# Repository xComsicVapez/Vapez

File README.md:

# Vapez

## Wooting 60HE — Apex Superglide DKS

Profile + setup for one-key superglides on **`C`** at **240 FPS** (Jump=`Space`, Crouch=`Left Ctrl`):

→ [`wooting-apex-superglide/`](./wooting-apex-superglide/)

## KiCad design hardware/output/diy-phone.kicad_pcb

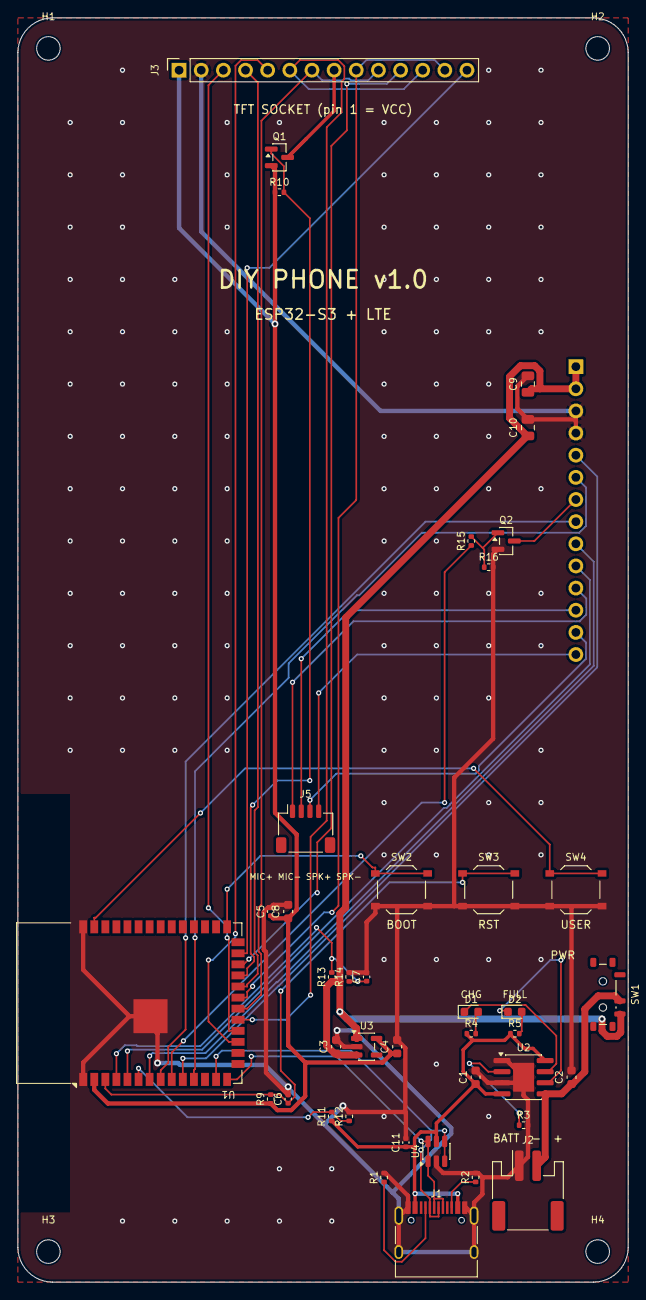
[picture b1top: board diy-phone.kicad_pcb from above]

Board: 2 copper layers, 70.0 x 145.0 mm, 45 parts (1 on the bottom side), 41 nets.

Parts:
C1, C2, C3, C4, C8: 10uF; C_0603_1608Metric
C5, C7, C11: 100nF; C_0402_1005Metric
C6: 1uF; C_0402_1005Metric
C9, C10: 22uF; C_0805_2012Metric
D1: CHRG red; LED_0603_1608Metric
D2: FULL green; LED_0603_1608Metric
H1, H2, H3, H4: M2.5; MountingHole_2.7mm_M2.5
J1: USB-C; USB_C_Receptacle_HRO_TYPE-C-31-M-12
J2: Battery JST-PH; JST_PH_S2B-PH-SM4-TB_1x02-1MP_P2.00mm_Horizontal
J3: TFT 1x14 socket; PinSocket_1x14_P2.54mm_Vertical
J4: LTE 1x14 socket; PinSocket_1x14_P2.54mm_Vertical
J5: Earpiece/Mic JST-SH; JST_SH_SM04B-SRSS-TB_1x04-1MP_P1.00mm_Horizontal
Q1: AO3401A; SOT-23
Q2: MMBT3904; SOT-23
R1, R2: 5.1k; R_0402_1005Metric
R3: 1.2k; R_0402_1005Metric
R4, R5, R15: 1k; R_0402_1005Metric
R9, R10, R16: 10k; R_0402_1005Metric
R11, R12, R13, R14: 100k; R_0402_1005Metric
SW1: POWER; SW_SPDT_Shouhan_MSK12C02
SW2: BOOT; SW_Push_1P1T_XKB_TS-1187A
SW3: RESET; SW_Push_1P1T_XKB_TS-1187A
SW4: USER; SW_Push_1P1T_XKB_TS-1187A
U1: ESP32-S3-WROOM-1-N16R8; ESP32-S3-WROOM-1
U2: TP4056; SOIC-8-1EP_3.9x4.9mm_P1.27mm_EP2.41x3.3mm
U3: ME6211C33; SOT-23-5
U4: USBLC6-2SC6; SOT-23-6

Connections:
3V3: C4.1, C5.1, C8.1, J3.1, Q1.2, R9.1, R10.1, U1.2, U3.5
BAT+: C2.1, J2.2, SW1.2, U2.5
BOOT: SW2.1, U1.27
BTN_USER: SW4.1, U1.39
CC1: J1.A5, R1.1
CC2: J1.B5, R2.1
CHRG_N: D1.1, U2.7
EN: C6.1, R9.2, SW3.1, U1.3
GND: C1.2, C2.2, C3.2, C4.2, C5.2, C6.2, C7.2, C8.2, C9.2, C10.2, C11.2, J1.A1, J1.A12, J1.B1, J1.B12, J1.S1, J2.1, J3.2, J4.3, J4.4, Q2.2, R1.2, R2.2, R3.2, R12.2, R14.2, R16.2, SW2.2, SW3.2, SW4.2, U1.1, U1.40, U1.41, U2.1, U2.3, U2.9, U3.2, U4.2
LCD_BL_N: Q1.1, R10.2, U1.23
LCD_CS: J3.3, U1.18
LCD_DC: J3.5, U1.17
LCD_LED: J3.8, Q1.3
LCD_RST: J3.4, U1.22
LED_CHRG_A: D1.2, R4.2
LED_STDBY_A: D2.2, R5.2
MIC_N: J4.12, J5.2
MIC_P: J4.11, J5.1
MODEM_DTR: J4.9, U1.7
MODEM_PWRKEY: J4.7, Q2.3
MODEM_PWR_ON: R15.1, U1.9
MODEM_RI: J4.8, U1.8
MODEM_RXD: J4.5, U1.10
MODEM_STATUS: J4.10, U1.5
MODEM_TXD: J4.6, U1.11
PROG: R3.1, U2.2
Q2_BASE: Q2.1, R15.2, R16.1
SPI_MISO: J3.9, J3.13, U1.21
SPI_MOSI: J3.6, J3.12, U1.19
SPI_SCK: J3.7, J3.10, U1.20
SPK_N: J4.14, J5.4
SPK_P: J4.13, J5.3
STDBY_N: D2.1, U2.6
TOUCH_CS: J3.11, U1.24
TOUCH_IRQ: J3.14, U1.25
USB_DN: J1.A7, J1.B7, U1.13, U4.3, U4.4
USB_DP: J1.A6, J1.B6, U1.14, U4.1, U4.6
VBAT_SENSE: C7.1, R13.2, R14.1, U1.4
VBUS: C1.1, C11.1, J1.A4, J1.A9, J1.B4, J1.B9, R4.1, R5.1, R11.1, U2.4, U2.8, U4.5
VBUS_SENSE: R11.2, R12.1, U1.6
VSYS: C3.1, C9.1, C10.1, J4.1, J4.2, R13.1, SW1.3, U3.1, U3.3

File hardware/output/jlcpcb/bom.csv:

Comment,Designator,Footprint,LCSC Part #
10uF,"C1,C2,C3,C4,C8",C_0603_1608Metric,C19702
100nF,"C5,C7,C11",C_0402_1005Metric,C1525
1uF,C6,C_0402_1005Metric,C52923
22uF,"C9,C10",C_0805_2012Metric,C45783
CHRG red,D1,LED_0603_1608Metric,C2286
FULL green,D2,LED_0603_1608Metric,C12624
USB-C,J1,USB_C_Receptacle_HRO_TYPE-C-31-M-12,C165948
Battery JST-PH,J2,JST_PH_S2B-PH-SM4-TB_1x02-1MP_P2.00mm_Horizontal,C295747
Earpiece/Mic JST-SH,J5,JST_SH_SM04B-SRSS-TB_1x04-1MP_P1.00mm_Horizontal,C160404
AO3401A,Q1,SOT-23,C15127
MMBT3904,Q2,SOT-23,C20526
5.1k,"R1,R2",R_0402_1005Metric,C25905
1.2k,R3,R_0402_1005Metric,C25862
1k,"R4,R5,R15",R_0402_1005Metric,C11702
10k,"R9,R10,R16",R_0402_1005Metric,C25744
100k,"R11,R12,R13,R14",R_0402_1005Metric,C25741
POWER,SW1,SW_SPDT_Shouhan_MSK12C02,C431540
BOOT,SW2,SW_Push_1P1T_XKB_TS-1187A,C318884
RESET,SW3,SW_Push_1P1T_XKB_TS-1187A,C318884
USER,SW4,SW_Push_1P1T_XKB_TS-1187A,C318884
ESP32-S3-WROOM-1-N16R8,U1,ESP32-S3-WROOM-1,C2913202
TP4056,U2,SOIC-8-1EP_3.9x4.9mm_P1.27mm_EP2.41x3.3mm,C16581
ME6211C33,U3,SOT-23-5,C82942
USBLC6-2SC6,U4,SOT-23-6,C7519

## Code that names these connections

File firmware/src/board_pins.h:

#pragma once
// GPIO map of the DIY phone mainboard (see hardware/phone_design.py).
// Display SPI pins are configured for TFT_eSPI in platformio.ini.

// Cellular module socket J4
constexpr int PIN_MODEM_TX = 17;      // ESP32 TX -> module RXD
constexpr int PIN_MODEM_RX = 18;      // ESP32 RX <- module TXD
constexpr int PIN_MODEM_PWRKEY = 16;  // drives an NPN that pulls PWRKEY low
constexpr int PIN_MODEM_RI = 15;
constexpr int PIN_MODEM_DTR = 7;
constexpr int PIN_MODEM_STATUS = 5;
constexpr uint32_t MODEM_BAUD = 115200;

// Display backlight: P-MOSFET high side switch, LOW = on
constexpr int PIN_LCD_BL_N = 21;
constexpr int PIN_TOUCH_IRQ = 48;

// Buttons (active low, internal pull-ups)
constexpr int PIN_BTN_BOOT = 0;
constexpr int PIN_BTN_USER = 1;

// 100k/100k dividers
constexpr int PIN_VBAT_SENSE = 4;
constexpr int PIN_VBUS_SENSE = 6;
constexpr float SENSE_DIVIDER = 2.0f;
